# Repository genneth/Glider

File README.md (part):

# Glider

Open-source Eink monitor with an emphasis on low latency.

Note: This repo only contains the hardware design, the gateware running on the FPGA is my open-source [Caster EPDC](https://gitlab.com/zephray/Caster/) design. This README also contains information about the Caster as well.

This is a long document, containing not just information about this project, but also pretty much everything I know about Eink. Given it's a bit hard to gather information about Eink online, I think this is the right thing to do. Use the following table of contents to navigate around.

Eink is a registered trademark and brand of E Ink Corporation. All the contents provided in this repo are based on publicly available information online and original research. They are not endorsed by Eink in any way and they may contain errors and/ or inaccuracies. 

If you're interested in attaining a board, checkout the [product page for the Modos Paper Monitor on Crowd Supply](https://www.crowdsupply.com/modos-tech/modos-paper-monitor).

If you are interested in Eink or any other display technologies, I have a Discord server for that. Feel free to join: [https://discord.gg/rtT7euSHQS](https://discord.gg/rtT7euSHQS) . (This Discord server is also not endorsed by Eink or any other company. It's not a customer support server.) For Modos product support or other inqueries about Modos products, use [https://discord.gg/6ktE6VxSyh](https://discord.gg/6ktE6VxSyh).

## Table of Contents 

- [Overview](#overview)
    - [Features](#features)
    - [Hardware](#hardware)
    - [Components](#components)
- [Eink Screens](#eink-screens)
    - [Basic Theory of Operation](#basic-theory-of-operation)
    - [Advantages and Disadvantages](#advantages-and-disadvantages)
    - [The Role of Eink Controller](#the-role-of-eink-controller)
    - [Screen Panel Types](#screen-panel-types)
    - [Using Screen with Integrated Controller](#using-screen-with-integrated-controller)
    - [Using Screen without Integrated Controller](#using-screen-without-integrated-controller)
    - [Understanding Waveform](#understanding-waveform)
    - [Greyscale Display](#greyscale-display)
    - [Color Display](#color-display)
    - [Dithering](#dithering)
    - [Eink Screen Generations](#eink-screen-generations)
- [Caster/ Glider Design](#design-of-caster-and-glider)
    - [Low Latency Drive](#low-latency-drive)
    - [Hybrid Greyscale Mode](#hybrid-greyscale-mode)
    - [Limitations](#limitations)
    - [Hardware Design Decisions]()
    - [Gateware Architecture](#gateware-architecture)
    - [Firmware Functions](#firmware-functions)
    - [Resources Utilization](#resources-utilization)
- [Building](#building)
    - [PCB](#pcb)
    - [FPGA Bitstream](#fpga-bitstream)
    - [MCU Firmware](#mcu-firmware)
    - [Flashing Board](#flashing-board)
    - [Compatible Screens](#compatible-screens)
- [References](#references)
- [License](#license)
- [Appendix](#appendix)
    - [Using Screens without Datasheet](#using-screens-without-datasheet)
    - [Screen List](#screen-list)

## Overview

### Features

- Complete solution for low-latency/ high-refresh-rate EPD monitor
- Supports electrophoretic display panels with parallel I/F (Eink(R), OED and DES)
- Supports both monochrome and color-filter-array (such as Kaleido(TM)) based color screen
- Extremely low processing delay of \<20 us
- Supports binary, 4-level grayscale, and 16-level grayscale output modes
- Latency-optimized binary and 4-level grayscale driving modes
- Hybrid automatic binary and 16-level grayscale driving mode
- Host software runtime controllable regional update and mode switching
- Hardware bayer dithering, blue-noise dithering, and error-diffusion dithering with no additional latency
- Controller takes standard HVsync signal input
- Board-level design supports USB-C (USB Type-C DisplayPort Alt Mode) and DVI input

### Hardware

- Xilinx(R) Spartan-6 LX16 FPGA running Caster
- DDR3-800 framebuffer memory
- Type-C DisplayPort Alt-Mode video input with onboard PTN3460 DP-LVDS bridge or
- DVI (via microHDMI connector) video input with onboard ADV7611 decoder
- Epaper power supply with up to 1A peak current on +/-15V rail supporting large panels
- VCOM kick-back voltage measurement support
- On-board STM32H750 microcontroller for USB communication and firmware upgrade
- Up to 133MP/s processing rate with dithering enabled, >200MP/s when disabled

The board is designed with KiCad. You may need the latest stable version of KiCad to open the source file.

### Components

This repo hosts the PCB design and firmware source code. The RTL code is in a separate repo: [https://gitlab.com/zephray/Caster/](https://gitlab.com/zephray/Caster/).

## Eink Screens

Eink is the brand of a family of paper-like electrophoretic displays. The underlying technology is invented in the MIT Media Lab between 1995 and 1997 by Barrett Comiskey, J.D. Albert, and Joseph Jacobson. They later founded the E Ink Corporation to commercialize this technology.

Nowadays they are commonly used on e-readers and electronic shelf labels. You’ve probably seen them on Kindle, in stores, or maybe in some train stations as well.

| eReader/ Tablets | Electronic Shelf Label | Digital Signage |
|-|-|-|
|  |  |  |

(Source: https://www.eink.com/application, image copyright Eink corporation)

This section gives an overview of the electrophoretic displays, including the screen panels available and underlying technology. Note this project doesn't and can't support all electrophoretic screens. This documentation also solely focuses on using existing off-the-shelf screen panels rather than the physics or manufacturing process of one.

### Basic Theory of Operation

In the simplest form, you have charged particles with different colors, dispersed in some oil in some transparent container. By applying electric fields the particles can be moved up or down to produce either black or white, or a mixture of that.

(Source: https://www.eink.com/tech/detail/How_it_works , copyright Eink Corporation)

There are multiple technologies based on this basic concept, namely Eink’s micro-capsule display, SiPix (now acquired by Eink)’s micro-cup display, and WFT’s DES display. They differ in specific ways of confining the particles in containers, but otherwise very similar.

The pixels on the screen are typically arranged as a 2D array, driven with TFTs. The pixels are scanned/ driven periodically at a fixed refresh rate, typically ranging from 50Hz to 120Hz. Applying positive voltage on the pixel will typically drive the particles toward the white state while applying negative voltage will drive the particles towards the black state. This is similar to active matrix TN/IPS LCDs, which also use 2D TFT arrays and electrical fields for changing state. However, unlike LCDs, EPDs maintain their state after the electrical field is removed. So unlike LCDs which require continuous refreshing, the EPDs only need to be refreshed till the pixels are fully driven.

In terms of driving the screen panel, depending on the pixel value (1 or 0), each pixel would be driven either with a positive voltage or a negative voltage. A global counter can be used to count the frames elapsed and stop driving the pixels after a predefined period of time (for example, 100ms). Two framebuffers are typically used for determining if the pixel has changed color or not. If not, then the pixel does not need to be driven.

### Advantages and Disadvantages

In terms of display quality, EPDs are no match for modern IPS LCDs. The following is a comparison table of key parameters. The specific number would vary depending on the screen used but should be within the same ballpark.

| | Monochrome EPD | CFA-based Color EPD | Transmissive TFT IPS LCD | Reflective TFT TN LCD |
|-|-|-|-|-|
| Contrast Ratio | ~17:1 | ~14:1 | ~1000:1 | ~14:1 |
| Colors | 16 (Greyscale) | 4096 | 16M | 256 |
| Color Gamut | N/A | ~1.5% sRGB | ~99.9% sRGB | N/A |
| Reflectivity | ~45% | ~25% | N/A | ~15% |
| Response Time | ~150ms | ~150ms | ~10ms | ~15ms |

It has a few advantages. It reflects lights instead of emitting lights, so it generally consumes less power and can be used outdoors, etc. It’s also bistable, which means that it retains the image after the power has been removed. Personally, the biggest differentiating factor for me (author of this README) is that it looks like paper.

The image above shows a comparison between reflective TFT LCD (SHARP memory LCD in this case) and Eink. The LCD has a mirror-like texture which changes reflectivity drastically in different angles, while the Eink is more paper-like.

| ZBD LCD | Ch LCD | STN LCD |
|-|-|-|
|  |  |  |
| Bistable, reflective, high contrast, no greyscale, ~10s refresh | Bistable, reflective, lower contrast, up to 32 level greyscale, ~5s refresh | Volatile, reflective, lower contrast, up to 32 level greyscale, ~100ms response |

There are many other reflective or bistable display technologies. They are all interesting displays on their own, but none of them feels like paper (yet).

Overall, there is no single perfect display technology. Each has its own unique strength. Pick the right one for your project.

### The Role of Eink Controller

The Eink controller is in some ways similar to the display controller (DC/ CRTC) + timing controller (TCON) in a typical LCD-based system. It takes the raw image data and converts it to signals required to drive the screen.

To understand the actual work of an eink controller, start from the basic concept. The color of a pixel can be changed by applying positive or negative voltage for a finite period of time. From the controller’s perspective, depending on the current state of the pixel and the desired state of the pixel, there are 4 possibilities.

| Current State | Target State | Action |
|-|-|-|
| Black | Black | No operation |
| Black | White | Apply positive voltage |
| White | Black | Apply negative voltage |
| White | White | No operation |

The controller needs to store and maintain the screen state inside of its own buffer memory, so it would typically have a large on-chip SRAM or an off-chip SDRAM controller. The controller should also have a timer to ensure the screen doesn't get overdriven or underdriven.

The controller often uses the so-called "[waveform](#understanding-waveform)" to replace the action column of the previous table. Instead of hardcoding the action for state transition, the actions are stored into a look-up-table (LUT) which can be modified at runtime to allow higher flexibility.

Controllers may also offer more advanced features such as [dithering](#dithering) acceleration, multiple region updates, automatic LUT selection, etc.

### Screen Panel Types

As discussed in the previous section, an Eink screen needs to be coupled to an Eink controller to function. Aside from that, the screen also needs high-voltage drivers to drive the TFTs and the pixels. Virtually all E-paper panels use either COG (Chip-on-Glass) or TAB (Tape Auto Bonding) to integrate some chips onto the screen panel itself. Most of the screens available today can be divided into two categories based on whether or not the controller is integrated in:

Here is a non-exhaustive list of the types based on their size: (the size or resolution is not related to or limited by the type, it is just for a certain size, and the vendors tend to make them the same type.)

- Screens without controller: 4.3", 6.0", 7.8", 8.0", 9.7", 10.3", 13.3", 25.3", 31.2", 42"
- Screens with controller: 1.02", 1.54", 2.13", 2.6", 2.9", 3.71", 4.2", 5.65", 5.83", 7.5", 12.48"

One may notice that almost all e-readers/ e-ink cellphones use screens without controllers, while almost all e-ink electronic shelf labels (ESL) use screens with controllers. This gives some hints about the advantages and disadvantages of two types:

| | Without Controller | With Controller |
|-|-|-|
| System Cost | High. A dedicated controller or SoC with an integrated controller is usually required. Needs a dedicated power supply. | Low. Virtually any MCU could drive the screen directly, and the power supply is integrated in. |
| Greyscale Levels | Generally 16 (4bpp), up to 32 (5bpp) | Generally 2 (BW only) or 4 (2bpp), with some hack, up to 16 (4bpp) |
| Refresh Speed | Generally fast (100ms~300ms) for BW. Depends on the screen used and the system architecture | Generally fast (100ms~300ms) for BW if the partial refresh is enabled. Greyscales are much slower, BWR or BWY screens would be even slower.
| Total Update Latency | Generally the same as refresh time. Depends on the system architecture | Slow. Ranging from 100ms to several seconds based on the resolution. |

Please keep in mind the discussion is about off-the-shelf screens you can buy today. These tradeoffs do not necessarily come from the fact the controller is integrated or not.

Note that I mentioned the refresh speed and total update latency. They are different:

The refresh speed refers to the time it takes to start refreshing the screen: from starting to seeing screen changing, to the screen finish showing the new content.

The total update latency refers to the latency when the processor needs to update the screen, to the screen finish showing the new content. As you can see, this is the biggest issue for screens with controllers. This is the main reason why they are rarely used on e-readers cell phones or PC monitors.

This diagram illustrates the difference between the two. It should be noted that the screens without controllers have the flexibility to be driven quickly, but the system designer might not architect the system for low latency.

### Using Screen with Integrated Controller

Screens with integrated controllers have almost everything already integrated. Common display panels of this type only need a few external capacitors, inductors, and MOSFETs to support the integrated bipolar power supply circuit, then it could be hooked up to MCUs or MPUs using common interfaces like SPI or I2C. There are a lot of driving boards and examples of these screens available online.

To be expanded (TODO)

### Using Screen without Integrated Controller

This could get complicated. Note I used a lot of "generally" in the previous comparison table because there are many things one could do to drive them. Some of them would certainly impact the performance. The main issue here is the controller chip. There are three solutions to drive these screens:

- Using a dedicated controller chip to drive the screen
- Using an SoC that has an integrated controller
- Using a fast MCU/SoC to emulate the controller with GPIO (software timing controller)

Then, again here is a comparison between them:

| | Specialized controller chip | SoC with integrated controller | MCU + Software TCON |
|-|-|-|-|
| Resolution | UXGA+ | UXGA+ | Limited by MCU RAM. Up to XGA with SRAM, UXGA with PSRAM, UXGA+ with DDR |
| Greyscale | Up to 32 | Up to 32 | Up to 32 |
| Partial Update | Yes | Yes | Yes |
| Total Update Latency | Depends. Could be very close to refresh speed, could be slow like screens with controller | Same as refresh speed | Same as refresh speed if data is internally generated (not streaming from an external device such as a PC) |
| Suitable Applications | IoT devices, E-readers, cellphones, E-ink monitors. possibly E-ink laptops | Advanced IoT devices, E-readers, cellphones, E-ink typewriters, possibly lower performance E-ink laptops | When using MCU: IoT devices, large ESLs, simple DIY E-readers. When using MPU: Same as SoC with integrated controller |

When using a dedicated controller, it could accept data from external devices. This allows it to be used in various different types of applications. Ranging from IoT devices, and ESLs, to PC monitors with relatively fast refresh rate and low latency.

When using SoC or MCU, the display content is generated by the SoC or MCU itself, which ultimately is limited by the capability of the SoC or MCU. Given the current SoCs with E-ink display controllers are usually limited in performance, the application is limited. The same goes for MCU, it does what an MCU could do. You could find ways to stream video data into SoC or MCUs by using USB, camera interface, WiFi, etc., but this might not be optimal.

#### Existing Solutions

- Specialized controller chip
    - Closed-source
        - EPSON S1D13xxx: Widely used EPD controller in early E-readers. Proprietary, no documents available. Probably EOL.
        - IT8951: Used on the waveshare EPD Hat. Documents are available. It works with large EPDs up to 2048x2048. The drawback is the speed as the interface between processor and IT8951 could be slow. This is similar to the situation on screens with integrated controller
        - T1000: Also known as IT8957, upgraded model of IT8951. It supports even higher resolution. It features a higher speed MIPI DSI interface to mitigate the slow speed of IT8951.
        - Waveshare HDMI driver board: FPGA-based controller. Closed source but easily purchasable, could be integrated into larger projects as a module.
    - Open-source
        - This project (Caster + Glider): FPGA-based controller, multiple update modes, ultra-low latency processing, and wide range of screen support.
        - https://hackaday.io/project/21607-paperback-a-desktop-epaper-monitor: FPGA-based controller. However, doesn't support partial update mode and slower speed.
        - https://hackaday.io/project/21168-fpga-eink-controller: FPGA-based controller supports vendor waveform with reasonable speed.
- SoC with integrated controller
    - RK29xx: Fairly old, Cortex-A8 based (RPi 1 level performance), 55nm, EOL
    - RK3026/RK3028: Fairly old, Cortex-A9 based (RPi 2 level performance), 40nm, EOL
    - i.MX 50: Fairly old, Cortex-A8 based (RPi 1 level performance), 65nm, in production
    - i.MX 6ULL: Cortex-A7 based (RPi 1 level performance), 40nm, in production
    - i.MX 6S/D: Fairly old, Cortex-A9 based (RPi 2-3 level performance), 40nm, in production
    - i.MX 7S/D: Cortex-A7 based (RPi 2 level performance), 28nm, in production
    - i.MX 8ULP: Cortex-A35 based (RPi 2 level performance), 28nm FD-SOI, in production
    - AW B200: Cortex-A53 based (RPi 2 level performance), 28nm, in production
    - MT8113: Cortex-A53 based (RPi 2 level performance), 12nm, in production
    - RK3566/RK3568: Cortex-A55 based (RPi 3 level performance), 22nm, in production
    - RK3576: Cortex-A72 + A53 based (RPi 4-5 level performance), 8nm, in production
- MCU/SoC + Software TCON
    - http://essentialscrap.com/eink/waveforms.html: One of the earliest e-ink hacks. Limited in performance but still could be used as a reference
    - NekoCal: One of the earliest e-ink software TCON with greyscale support. Used to be available as a DIY kit. No longer updated, still could be used as a reference
    - InkPlate 6/10: Commercially available. Based on ESP32.
    - EPDiy: Based on ESP32, supports a lot of different screens, recommended if want to build some device with ESP32+Eink or embed it into a larger project.

#### Interface Signals and Timing

The interface signals and timing are fairly similar to LCDs without a controller. Following is the list of signals typically found on EPDs:

- GDOE/ MODE: Gate driver output enable
- GDCLK/ CKV: Gate driver clock (like HSYNC in LCD)
- GDSP/ SPV: Gate driver start pulse (like VSYNC in LCD)
- SDCLK/ XCL: Source driver clock (like PCLK in LCD)
- SDLE/ XLE: Source driver latch enable (like HSYNC in LCD)
- SDOE/ XOE: Source driver output enable
- SDCE/ XSTL: Source driver start pulse (like DE in LCD)
- SD: Source driver data (8-bit or 16-bit)

SD signals go into the source driver, typically in the X direction. GD signals go into the gate driver, typically in the Y direction. It's a 2D array, the gate driver selects one line at a time, and the source driver outputs the voltage for all the pixels in that line.

Conceptually, it's like a raster scan on a CRT. To send one field of data, both GD and SD are reset to the start position by using the start pulse signal. Data are then transmitted into the source driver 4 or 8 pixels at a time. Once the line has been fully transmitted, the source driver is reset to the beginning position by a start pulse signal, and the gate driver moves to the next line by a pulse on the gate driver clock. Once all lines have been scanned, the entire process repeats for the next field.

One notable difference with LCD is that each pixel is represented by 2 bits. This, however, doesn't mean each pixel is 2bpp or 4-level greyscale. The 2-bit per pixel is used to encode the voltage applied to the pixel:

- 00: No voltage
- 01: Negative voltage
- 10: Positive voltage
- 11: No voltage

Just like CRT/ LCD, there are also blanking periods in the entire timing (which means it's just waiting without active pixel data being sent). They have identical meanings to CRT/ LCD systems:

(Source: https://projectf.io/posts/video-timings-vga-720p-1080p/, Copyright Will Green)

The following is a piece of pseudo-code implementing the Eink timing:

```c
#define DATA_BUS_WIDTH      8 // 8bit wide bus
#define PIXEL_PER_CYCLE     (DATA_BUS_WIDTH / 2)
#define VFP     12  // Vertical front porch
#define VSYNC   1   // Vertical sync length
#define VBP     2   // Vertical back porch
#define VACT    758 // Vertical active lines
#define HFP     72  // Horizontal front porch
#define HSYNC   2   // Horizontal sync length
#define HBP     2   // Horizontal back porch
#define HACT    (1024 / PIXEL_PER_CYCLE)

void pulse_h_clock() {
    sdclk = 1;
    sdclk = 0;
}

void drive_line(bool v_in_act) {
    sdce = 1;
    gdclk = 0;
    for (int i = 0; i < HFP; i++) pulse_h_clock();
    sdle = 1;
    gdclk = 1;
    for (int i = 0; i < HSYNC; i++) pulse_h_clock();
    sdle = 0;
    for (int i = 0; i < HBP; i++) pulse_h_clock();
    if (v_in_act) sdce = 0;
    for (int i = 0; i < HACT; i++) {
        send_data();
        pulse_h_clock();
    }
}

void drive_frame() {
    gdoe = 0;
    sdoe = 0;
    gdsp = 1;
    for (int i = 0; i < VFP; i++) drive_line(false);
    gdsp = 0;
    gdoe = 1;
    sdoe = 1;
    for (int i = 0; i < VSYNC; i++) drive_line(false);
    gdsp = 1;
    for (int i = 0; i < VBP; i++) drive_line(false);
    for (int i = 0; i < VACT; i++) drive_line(true);
}
```

More explanation can be found at [http://essentialscrap.com/eink/index.html](http://essentialscrap.com/eink/index.html)

### Understanding Waveform

The waveform is a look-up table for the eink controller to determine how to drive the pixels, mostly useful for greyscale image display, but generally used for binary image display as well.

The look-up-table has 3 inputs (dimensions): frame number, source grayscale level, and destination grayscale level. During the update process, for a certain pixel, the source and destination level stays the same, and the frame number increases each frame. The look-up process is done for every pixel every frame. The controller may choose different LUTs depending on the ambient temperature. Mode switching is also implemented by simply switching between different LUTs.

This is essentially what typically eink controller does. For each pixel, look up in the table to determine the voltage to use. Repeat this for a couple of frames with an incrementing frame counter, until all pixels are fully driven.

It should be obvious that the waveform file itself is independent of the resolution as the waveform only cares about a single pixel. With an incorrect or un-optimal waveform, the screen should at least display some recognizable image.

#### Waveform Example

There are several sample waveform tables provided in the project repo. Take the GC16 (Greyscale clearing 16-level) waveform of GDEW101C01 as an example: https://github.com/zephray/NekoInk/blob/master/waveform/gdew101_gd/test_M2_T0.csv

Take one line from that file:

```6,13,0,0,0,0,0,0,0,0,0,2,1,1,1,1,1,1,1,1,1,1,2,2,2,2,2,2,2,2,2,2,2,2,2,2,2,2,1,0```

This means from greyscale level 6 to level 13, it needs to go through the following sequence. Each number means the operation on that frame, 0 is no-operation, 1 is darken, and 2 is lighten. In this case, there are 38 frames, first 9 frames do nothing, then lighten for 1 frame, darken for 10 frames, lighten for 16 frames, and finally darken for 1 frame and have no operation for the last frame. This is the sequence to change a pixel from level 6 to level 13. Such lookup is done for every pixel on every frame.

#### Waveform Modes

To give system designers more flexibility, Eink controllers often offer multiple "modes", like binary mode, 16-level grayscale mode, 16-level grayscale mode with reduced flashing, 4-level grayscale mode, etc.

The waveform provided by Eink has many modes. There is a good document from Eink describing the modes:

https://www.waveshare.net/w/upload/c/c4/E-paper-mode-declaration.pdf

It provides a good overview of the modes. I am just going to add some comments.

- GC in the GC16 stands for "greyscale clearing". GC does not stand for greyscale. There are 16-level greyscale modes that aren't called GC16.
- Officially there are no 32-level greyscale modes (yet). There are 5-bit waveforms, which means they internally use 5 bits for each pixel, which potentially allows up to 32-level greyscale, but no such waveform exists (yet).
- There are no 16-level greyscale modes without flashing. The DU4 is the only greyscale mode that's non-flashing.
- The GL16 mode, as described, only works for black text on a white background. When refreshing greyscale images, the GL16 is similar to the GC16.
- The GLR16 mode is also called the REGAL mode, and the GLD16 mode is also called the REGAL-D mode.
- Eink doesn't even know if it should be spelled as REAGL or REGAL:  Google search "REAGL site:eink.com" and "REGAL site:eink.com" both returned several results.
- Eink-provided waveform usually implements all these modes, however it is not always required. The waveform file may also contain waveform tables in other orders.
- In terms of the waveform, the waveform for GL16, GLR16, and GLD16 are identical. This is expected, the REGAL requires an additional algorithm on the host image processing and is not a technology based on tweaking the waveform.

#### Obtaining Waveform

In general, the screen vendor (Eink, Good Display, etc.) should provide the waveform file.

If your screen has a flash chip on it, it's also possible to extract the waveform from a flash dump:

```dd if=somedump.bin of=waveform.wbf bs=1 skip=2182```

If you have access to an application board, it might also be possible to extract the waveform there. For example, if the system uses a T1000/T2000/T2001 controller, the waveform is usually stored in the SPI flash connected to the controller. Some times the waveform stored on the flash is compressed (in addition to the RLE compression already applied to the waveform file itself).

#### Waveform Formats

E-Ink distributes waveforms in the wbf file format. SoC/ Eink controller hardware often requires converting the file into a vendor-specific file format. Caster/ Glider also uses a specific binary format. This project defines a common human-readable format (Interchangeable Waveform Format, IWF) and provides several tools for working with different binary formats and the IWF format.

#### Interchangeable Waveform Format

The waveform consists of one descriptor file in iwf extension (ini format) and various lut data files in csv format.

The descriptor contains the following required fields:

- VERSION: the version of the descriptor (should be 2.0)
- NAME: (optional) original name for the waveform
- BPP: (optional, default 4) 4 or 5, representing the internal state count used for waveform
- PREFIX: the filename prefix for actual waveform files
- MODES: the total modes supported by the waveform
- TEMPS: the total number of temperature ranges supported by the waveform
- TxRANGE: the supported temperature in degC, where x is the temperature ID
- TUPBOUND: (optional) upper bound for temperature range, each range is TxRANGE to Tx+1RANGE (or TUPBOUND in case of the last one)
- TABLES: total number of LUTs inside the waveform
- TBxFC: the frame count for the table, where x is the LUT ID

Each mode has its own mode section named [MODEx], where x is the mode ID, containing the following fields:

- NAME: the name for that mode
- T*TABLE: the table used for the temperature in that mode

There should be a number of LUTs, saved in the filename like PREFIX_TBx.csv, where x is the LUT ID. Each csv file should contain a LUT like this: lut[src][dst][frame], which means, to transition from src greyscale level to dst greyscale level, at a certain frame in a frame sequence, what voltage should be applied to the screen (0/3: GND / Keep, 1: VNEG / To black, 2: VPOS / To white). Each line contains the frame sequence for one or more source-to-destination pairs.

For example:

- ```4,7,1,1,1,0,2``` means to transition from greyscale level 4 to greyscale level 7, there should be 5 frames, each applying VNEG VNEG VNEG GND VPOS
- ```0:14,15,2,2,2``` means to transition from any greyscale level between 0 and 14 to greyscale level 15, there should be 3 frames, each applying VPOS VPOS VPOS

These are provided to only illustrate the file format, they are not valid or meaningful Eink driving sequences.

#### Converting Between Waveform Formats

The following converters are provided in the repo:

- To convert from iwf to fw (iMX6/7 EPDC format): ```./mxc_wvfm_asm v1/v2 input.iwf output.fw```
- To convert from fw to iwf: ```./mxc_wvfm_dump v1/v2 input.fw output_prefix```
- To convert from wbf to iwf: ```./wbf_wvfm_dump input.wbf output_prefix```

#### Waveform Tweaks

Some commercial implementations allow users to reduce the frame count and/ or alter the waveform playback speed, so the user can trade between contrast ratio and frame rate.

### Greyscale Display

Other than full white and full black, with appropriate modulation, Eink screens can also display some levels of greyscale (typically 16).

For grayscale displays, the basic idea is simple. If the pixel is not fully driven (say only drives for 50ms while it takes 100ms to reach full black/ white), it would stay in a gray state.

There are two ways of achieving this modulation:
- Modulate the frame time
- Modulate the number of frames with constant frame rate

Both are possible, as described below

#### Frame Time Modulation

This method changes the drive time by changing the length of a single frame. The screen would only be driven for 15 or 31 frames for 16-level and 32-level greyscale, but the frame time (thus frame rate) is altered to provide the desired driving time. The LUT would be a one-dimension look-up table, only containing the incremental time required to drive to the next greyscale level. The source/ gate driver output enables the line to be toggled to achieve the desired driving time.

This method doesn't seem to be implemented in any commercial solutions and is significantly slower than the second method. But it certainly works. The 32-level greyscale demo shown in the picture above is achieved using this method.

#### Frame Count Modulation

This method changes the drive time by changing the number of frames being applied to the screen. The screen is still being driven at a constant frame rate. The following is a simplified hypothetical waveform table for achieving 4-level greyscale:

| Previous State | Target State | Frame 0 | Frame 1 | Frame 2 | Frame 3 | Frame 4|
|-|-|-|-|-|-|-|
| Black | Black | NOP | NOP| NOP | NOP | NOP |
| Black | Dark Grey | VPOS | VNEG | VPOS | NOP | NOP |
| Black | Light Grey | VPOS | VNEG | VPOS | VPOS | NOP |
| Black | White | VPOS | VNEG | VPOS | VPOS | VPOS |

Note how it alternates between VPOS and VNEG in the beginning. This is often called the "activation phase" to improve the contrast ratio. Putting this detail aside, it changes the number of VPOS frames to settle down on different grey levels.

The actual grayscale driving sequence used in the commercial implementation is more complex than that, often involving switching the pixel towards black/white a few times before settling. This design is partially due to the limited time control granularity and other temperature/ manufacturing variance-related concerns. Some side-effects of such a driving sequence are that the refreshing process is “flashing”, and is slower compared to displaying only a 1-bit binary image.

### Color Display

There are several different technologies that could be used to build full-color EPDs. The 2 most common ways are to use a color-filter-array (CFA) or use a multi-pigment color display.

The following picture has a CFA-based color screen (Kaleido 3) on the left, and a multiple pigment color display (Spectra 6) on the right, displaying the same image.

(Yes the left one IS a color screen!)

#### Color Filter Array

CFA stands for color filter array, which is colored glass/ film on top of the screen pixel. This is also the technology used on most color LCDs. Eink Kaleido, Eink Triton, and color DES are based on this technology. The main advantage is that it's relatively simple to control, and the low-level driving is the same with the greyscale panels. Thus it has the same level of refreshing time (100~200ms), and the same level of greyscale (16 level translate to 16^3=4096 colors). The drawback is that the CFA filters out some light (due to its colored nature), and the screen reflectivity is negatively affected by the CFA. The screen ends up being quite dark. Up to now, most color E-readers use CFA-based displays. This project supports all three major types of CFA-based EPD screens: color DES screen, Eink Triton, and Eink Kaleido.

#### Case Study: GDEW101C01 (CFA-based, DES)

The GDEW101C01 is a 10.1" color DES screen made by Good Display / WeiFeng Tech. It uses CFA to produce color images. As a result, to the eink controller hardware, it's just a normal greyscale panel with a bunch of pixels. However, the pixels are colored depending on their location due to the CFA. The coloring of the pixels can be either handled by hardware or software.

##### Pixel Arrangement

Color DES is a bit different from a typical color TFT LCD in terms of CFA design. Typically on TFT LCDs, one RGB pixel is called a pixel, and each R/G/B component is called as a sub-pixel. On color DES, the sub-pixel ends up being called a pixel, and each pixel is either red, green, or blue. In the display industry, such pixels are more commonly referred to as dots.

Pengo, CC BY-SA 3.0 https://creativecommons.org/licenses/by-sa/3.0, via Wikimedia Commons

The actual photo of the DES panel under the microscope:

In the above photo, the DES pixel arrangement is the same as the OLPC XO-1. Notably, many Eink's Kaleido 3 (but not all) also uses the same pixel arrangement.

Having no subpixel / each pixel only has 1 color doesn't necessarily mean that the effective resolution needs to be divided by 3. This arrangement is slightly more "efficient" than the RGB strip in terms of perceptive resolution. You can find a more detailed analysis in the paper Comparing the Effective Resolution of Various RGB Subpixel Layout.

##### Processing image for Color DES

If the image is displayed on color DES without any processing, it would look like a greyscale image. This is similar to when you just send the same color value to R/G/B components on a color LCD.

To get color, there are 2 possible solutions:
- Treat 4 pixels as a group of a single pixel, and each physical pixel is now considered as a subpixel.
- Treat each pixel as an independent pixel, but send only the color component that corresponds to the pixel color.

Depending on how you classify pixel and subpixel, the 2nd method can also be viewed as a mean of 2X supersampling subpixel rendering.

In general the 2nd method offers better resolution especially in text:

| Method 1 | Method 2 |
|-|-|
|  |  |

The following discussion are all about the 2nd method: render at full resolution, but only use 1 color component for each pixel.

(Source: https://wiki.laptop.org/go/File:PixelLayoutDiagonal.png, public domain)

For example, for pixel 01, the pixel on the screen is green. Then only the green component from the frame buffer should be sent to the screen.

To get a basic 4096 color image display, this is everything needed. However generally to improve image quality, a few more steps are applied:

##### Low pass filtering

The previously described image-displaying process is essentially a down-sampling process for each color component: Only 1/3 of the pixels are sent to the screen. Then this becomes a classic signal processing issue: sampling the signal would cause frequency components above Nyquist to fold back to the low frequency part. Or in simpler words, you would see jagged edges/ aliasing, which are things that weren't present in the original image. To prevent this, low pass filtering (blurring) needs to be applied first to the image to remove these high-frequency components. The following diagram from the OLPC wiki shows a simple way of implementing a such filter:

(Source: https://wiki.laptop.org/go/File:PixelProcDiagonal.png, public domain)

##### Dithering

Dithering can be applied to further improve image quality. See the dithering section for more details.

#### Multi-Pigment Color Display

Another technology for implementing color EPD is by using a multi-pigment color display. This is a technology developed initially by SiPix and further improved by Eink. The basic idea is to use ink particles with different colors inside a single pixel. By applying a sequence of voltages, the ink particles can be arranged to display different colors.

(Source: https://www.eink.com/tech/detail/How_it_works , copyright Eink Corporation)

One major advantage of this solution is it can achieve higher resolution (because it doesn't have a CFA, so no resolution reduction), higher reflectivity (because it doesn't have a CFA, so no light loss), and higher color saturation (because it doesn't have a CFA, no need to play the reflectivity vs saturation trade-off game).

Eink has 2 lines of products using this Technology, Eink Gallery and Eink Spectra. The advantage is it's much brighter compared to CFA-based solutions. The disadvantage is it's much more difficult to drive, and quite slow: 1st /2nd gen Eink Gallery screen takes 30s (!) to refresh, and Spectra 6 Plus devices take 7s to refresh. It's possible to trade in some color saturation for higher speed, though still much slower than CFA-based solutions. The specific product lines will also be discussed in [Eink Screen Generations](#eink-screen-generations)

##### How ACeP Waveform Works

To be written (TODO)

##### How to get more colors on ACeP

This is possible with a modified waveform.

To be written (TODO)

##### Fast ACeP

While ACeP screens have been generally slow to refresh (15-30s), Eink has tried to improve that. In 2022 Eink released their Gallery 3 lines of ACeP screens, which promised sub 1 second update time. [ACeP was supposed to be the "next big thing" in ereader](https://arstechnica.com/gadgets/2022/04/new-e-ink-gallery-displays-could-finally-make-full-color-e-readers-good/). Back in the end 2022, Eink announced that ["Gallery 3 has moved into mass production, with customer products from Bigme, BOOX, iFlyTek, iReader, PocketBook, Readmoo, and AOC coming down the pipeline in 2023 and beyond"](https://www.e-ink-info.com/e-ink-gallery-3-acep-color-epaper-displays-move-mass-production).

How well does it do? Just talking about the screen, it's not looking good. It suffers from poor reflectivity and poor saturation to a point where it's not much better than Kaleido:

(Original illustration copyright MiHoYo)

The difference between Gallery 3 and Gallery Palette (which is supposed to be a lower-end product) is also stunning:

The one on the left is the Gallery 3 used on eReaders, and the one on the right (brighter and more saturated one) is the Gallery Palette used on ESLs. Though to be honest I hacked the right one a bit to display 512 colors opposed to the stock 7 colors. If Gallery 3 had the same image quality as previous ACeP/ Gallery screens, it would make sense to trade in response time for better image quality. But it doesn't.

##### Future of ACeP

While as previously referenced that Eink was hoping to ship lot of Gallery 3 based E-readers in 2023, 2023 passed with exactly one product, the Bigme Galy, with mixed receptions. Early 2024, it was announced that [Bigme Galy has been discontinued](https://goodereader.com/blog/electronic-readers/bigme-galy-is-discontinued), and [Eink has announced EOL for certain ACeP-based products](https://www.ineltek.com/wp-content/uploads/2024/04/EInk_AC073TC1_EOLNoticeLetter_notice_20240401.pdf). But ACeP is not dead yet.

Going forward, Eink has 3 different line-ups for different markets:
- Eink Marquee for outdoor signage
- Eink Spectra for electronic shelf labels and advertisements
- Eink Gallery for e-readers and e-notebooks

All of these lines are direct offspring of the original ACeP screens:
- Eink Marquee uses the same color composition as the ACeP, but replaces the SiPix-style micro-cup with micro-capsule
- Eink Spectra uses similar structure as the ACeP, but replaces color composition
- Eink Gallery is the original ACeP line up

In 2024, we saw the release of reMarkable Paper Pro, which is a 11.8" Gallery 3 e-notebook. ACeP screens are still in production and we might be able to see more products in the future.

##### Spectra 6

Compared to the Gallery lines, Spectra 6 uses a very similar multiple pigment system. But instead of using cyan, magenta, and yellow as the base colors, Eink switched to use red, yellow, and blue instead. Officially the color gamut volume stays the same, but the contrast ratio gets boosted up to 22:1 from 10:1, mainly due to darker black. Reflectivity stays the same at around 35%, lower than Carta products, but still far better than CFA based ones.

(TODO: Compare image quality between Sp6 and GalleryPlus)

### Dithering

Eink and DES panels typically only support up to 16 levels of greyscale with the vendor-provided waveform. To improve response time, or to avoid flashing images, a binary (1-bit, 2-level) display is also used. Dithering could be applied to produce better images (increasing SNR, in signal processing sense).

The following is applying dithering to a simple black-to-white gradient. Note the results are not optimal due to limitations in quantization and incorrect gamma correction. But the idea is the same.

| Original | Binary No-dithering | 2 Row Sierra Dithered |
|-|-|-|
|  |  |  |

Dithering can help when the screen has a native 16-level greyscale as well:

| Original | 16 Level Greyscale No-dithering | 16 Level Greyscale Dithered |
|-|-|-|
|  |  |  |

As you can see, the non-dithered image loses all the greyscale in between, while the dithered version on the right gives the illusion of greyscale while only using full black and full white colors.

To understand it further, take the following example:

Say the source image is 30% brightness (or 0.3). This cannot be displayed on a binary screen which can only display 0% (0.0, black) or 100% (1.0, white) brightness. A simple thresholding process is added to determine if the screen should display 0 or 1 by checking the incoming brightness. If it's less than 0.5 then the display brightness is rounded down to 0, otherwise 1. Because 0.3 is always lower than 0.5, the whole screen displays 0 (black).

This is less than ideal. A better way is to set around 30% of the pixel black, while 70% of the pixel white. Different dithering algorithms can be used to achieve this 30/70 distribution. Two common methods used are ordered dithering and error-diffusion dithering, which will be described below.

#### Ordered Dithering

The ordered dithering adds a pre-computed/ fixed texture to the image before the thresholding process. In other words, it basically adds some noise to the image. This may sound weird initially, but it should be easy to see the effect of noise in the example.

Using the example previously described displaying 30% brightness grey on a binary screen. The goal is to let the rounding process end up with 0 for 30% of the time and 1 for 70% of the time. This could be achieved by adding a noise. In the simplest case, a random number with a uniform distribution between [-0.5, 0.5] is added to the incoming brightness. The brightness has a value of 0.3, when adding this number to the random number, the random number now has a uniform distribution between [-0.2, 0.8]. The threshold is still set to 0.5, and now the probability distribution can be seen as below:

The pixel now has a 30% chance of being rounded up to 1, and a 70% chance of being rounded down to 0. Before dithering, it would always be rounded down to 0.

However, a purely random number is generally not the best noise to use. Bayer dithering matrix and blue noise are more commonly used, with the results as illustrated below. The idea is the same, but instead of adding random numbers, a pre-computed number from the Bayer dithering matrix (array) or blue noise texture (array) is added to the image.

| Random Dithering| Bayer Dithering | Blue-noise Dithering |
|-|-|-|
|  |  |  |

#### Error-Diffusion Dithering

The basic idea is when rounding down the color (selecting the closest color from the 16-level greyscale from 256-level input), the error value (difference) is calculated and added to neighboring pixels (so this error would be considered when processing these pixels later). The whole process is called error-diffusion.

Still using the previous example of a 30% brightness image, and assume an extremely simple dither kernel: diffuse all error to the next pixel. Let's see it in action.

In the first pixel, 0.3 (image brightness) is less than 0.5 (threshold), so it's displayed as 0 (black). This introduces a 0.3 error: the displayed color is 0.3 darker than the requested color. So 0.3 is being diffused to the next pixel, hoping the next pixel can correct the error.

Onto the second pixel. The value is 0.3 (image brightness) + 0.3 (diffused error) = 0.6. It's now larger than 0.5 (threshold), so it's displayed as 1 (white). This introduces a -0.4 error: the displayed color is 0.4 brighter than the requested color. -0.4 will be diffused to the next pixel.

For the 3rd pixel, the value is now 0.3 - 0.4 = -0.1. This is less than 0.5 and displayed as 0 (black). Error -0.1 is diffused further.

And this process just goes on. With enough pixels, eventually, it would yield about 30% of white pixels and 70% of dark pixels.

Similar to how random value is not the best thing to do in ordered dithering, dithering to the right is also less than ideal. It creates very repetitive patterns. I mentioned the word kernel. Error diffusing uses a diffusion kernel, which specifies the target and percentage of the diffused error. There are many classic kernels, such as Floyd-Steinberg, Stucki, Sierra, etc. commonly used for image dithering. They all diffuse to more than 1 pixel to improve the overall look of the image. As shown below, even just diffusing the error to 2 pixels (half of the error goes to the pixel on the right, and the rest half of the error goes to the pixel on the bottom) yields a much better result:

| Dither to Right | Right and Down | Floyd-Steinberg |
|-|-|-|
|  |  |  |

#### Applying Dithering on CFA-based Color Screens

Dithering can be applied on CFA-based color screens such as Eink Kaleido and color DES screens as well. The following is on a simulated DES screen: (The left original is assuming the screen has a native 24bpp color, still on a simulated screen)

| 16M color DES (does not exist) | 8-color DES | 8-color DES Dithered |
|-|-|-|
|  |  |  |

Ordinary dithering kernels don't work too well on color screens. For example, the error-diffusion dithering process pushes/ diffuses error neighboring pixels without considering their color. Ideally, it should push/ diffuse the error only to pixels with the same color. This is fairly easy to fix though, by tweaking the kernel it would achieve good results on CFA-based screens as well. (I am going to shamelessly call it Wenting's kernel)

| 16M color DES (does not exist) | 8-color DES naively apply Floyd-Steinberg (wrong) | 8-color DES with Wenting's kernel |
|-|-|-|
|  |  |  |

Of course, one can apply Bayer-like ordered dithering, blue noise dithering, or dithering on 4096-color mode as well:

| 8-color DES Bayer-like | 8-color DES Blue-noise | 4096-color DES Error-diffusion |
|-|-|-|
|  |  |  |

It's called bayer because, similar to how naively doing error diffusion doesn't work, the bayer matrix has to be modified to work on the color screen.

#### Gamma Correction

Another thing to consider is gamma. The dithering process involves a step of selecting the closest value. However, selecting the closest numerical value does not necessarily mean the closest color. The image typically is in sRGB space, which is non-linear. This causes the simple rounding to pick the wrong color, also calculating the wrong error value. One solution is to work in the linear space. This is also known as gamma-aware dithering. You could read more related info online, for example here: [https://learnopengl.com/Advanced-Lighting/Gamma-Correction](https://learnopengl.com/Advanced-Lighting/Gamma-Correction).

The difference is quite evident when dithering down to 1 bit for a color screen. The top left is the original image, the top right is dithering in the sRGB space, and the bottom left is dithering in the linear space.

#### Further Reading

See [https://en.wikipedia.org/wiki/Dither](https://en.wikipedia.org/wiki/Dither) for more information about dithering.

### Eink Screen Generations

Depending on how you count, there are multiple generations of Eink screens commercially available. For monochrome screens before 2023, it's possible to tell the generation by looking at the 6th digit on the serial number:

That is the FPL code in the following table:

| FPL Platform | FPL Code | Panel Model    | Marketing Name          | First Introduced |
| ------------ | -------- | -------------- | ----------------------- | ---------------- |
| 2.0          | 0        |                |                         | ?                |
| 2.1          | 1        |                |                         | 2004             |
| 2.3          | 2        |                |                         | ?                |
| V100         | 3        |                | Vizplex                 | 2007             |
| V110         | 4        |                | Vizplex                 | 2008             |
| V110A        | 5        |                | Vizplex                 | 2008             |
| V220         | 6        | VA3200         | Pearl                   | 2010             |
| V250         | 7        |                | Pearl                   | ?                |
| V220E        | 8        |                | Pearl                   | ?                |
| V320         | 9, R     | VB3300         | Carta 1.2 / 1000        | 2013             |
| V320         | ?        | VB3300?        | Carta 1100              | 2019             |
| V400         | A, C     | VD1400/ VD1405 | Roadrunner / Carta 1200 | 2021             |
| V450         | ?        | VH1948         | Carta 1250              | 2021?            |
| ?            | ?        | VD1400/ VD1405 | Carta 1300              | 2023             |
| ?            | M        | ?              | Spectra (BWR)           | ?                |

Data points used to create the table above:
- The first commercialized Eink e-reader SONY Librie hit the market in 2004, *likely* with an ED060SC1 panel
- ED060SC1 has an FPL code of 1 on the barcode, meaning the 2.1 platform
- Multiple datasheets (like the one for ED060SC4) confirms the 6th digit marks the FPL code with mapping for V220/220E/320/400
- Inkwave's WBF decoder (originated from Kindle GPL kernel code) provides an FPL platform to an FPL code mapping table that matches well with info from the datasheet
- Kindle Oasis3 was reported to use a Carta 1100 screen, and it has an ED070KC3 screen with a V320 FPL platform
- Kindle PW5 was reported to use a Carta 1200 screen, and it has an ED068KC5 with a VD1405 panel model
- Kobo Clara BW was reported to use a Carta 1300 screen, and it has an ED060KHE with a VD1405 panel model
- The datasheet of ED068KC1 mentioned the name "Roadrunner" for the 400 platform, but that name never gets used outside of that. I would guess they were going to use the Roadrunner for the new generation but eventually fell back to Carta 1200 so it's more like an incremental improvement
- From the information available, it really looks like Carta 1000 and 1100 use the same film, and Carta 1200 and 1300 use the same film. If this is true, it may sound like a scam if they are named differently but use the same film. But this is actually okay. Just like how chips usually have a binning process, the same chip would sell under different product names with different performance levels. It's reasonable for Eink to do incremental improvements on the manufacturing process to yield better screens with the same film and call it under a different name, or simply binning screens to different grades and selling under different names.

I will let you decide how to count the generations.

For the CFA-based screens, the following generations of screens exist:

- Eink Triton: First generation color screen. Uses an RGBW glass color filter and square pixels. The underlying screen panel uses Pearl film.
- Eink Triton 2: 2nd generation color screen. Uses RGB glass color filter and stripe pixel. The underlying screen panel uses Pearl film.
- Eink Kaleido: 3rd or 2nd gen color screen depending on the definition. Uses an RGB color filter. Each pixel is still square, but each color covers 3 pixels. The underlying screen panel uses Carta film.
- Eink Kaleido Plus: 2nd gen Kaleido. Uses an RGB color filter. Each pixel is still square but different configurations exist. Some screens have each color covering 2 pixels, some others have each color covering only 1 pixel. The underlying screen panel uses Carta film.
- Eink Kaleido 3: 3rd gen Kaleido. There are at least 2 different configurations exist. One features RGB filter covering 1 pixel per color, the other features a 2R/2G/1B configuration, on average 5/3 pixels per color. The underlying screen panel uses Carta 1000/1200/1250/1300 film depending on the model.
- Eink Kaleido 3 Outdoor: Wide temperature version of Kaleido 3.

Most CFA-based color screen panels don't come with an integrated controller, but there are a few exceptions.

For the multiple-pigment color screens based on SiPix technology, the following generations of screens exist:

(Color abbreviation: B: black, W: white, R: red, Y: yellow, B: blue, C: cyan, M: magenta)

- Eink Spectra 3000: BWR or BWY 3 color screen.
- Eink Spectra 3100: BWRY 4 color screen.
- Eink Spectra 3100 Plus: BWRY 4 color screen. The orange display is now possible with driver circuit changes.
- Eink Spectra 6: RYBW 4 color screen. Can reproduce 6 primary different colors. Newer waveforms released by Eink increased this number to 10.
- Eink Spectra 6 Plus: RYBW 4 color screen. Still reproduces 6 different colors. Allows faster refresh compared to 6 with driver circuit changes.
- Eink Gallery (also known as Gallery 4000): CMYW 4 color screen (ACeP).
- Eink Gallery Plus (also known as Gallery 4000): CMYW 4 color screen (ACeP).
- Eink Gallery Palette (also known as Gallery Palette 4000)： CMYW 4 color screen (ACeP). Reproduce 7 different colors.
- Eink Gallery 3: CMYW 4 color screen (ACeP). Reproduce 8 different colors, much faster than other Gallery screens at the cost of lower saturation.

There are both integrated-controller Spectra/Gallery screens and controller-less Spectra/Gallery screens.

Additional notes regarding the multi-pigment color screens:

- ACeP, or Advanced Color ePaper refers to the CMYW 4 color screen. Is not a product line on its own
- To be honest, I don't know how many colors can be reproduced on Gallery or Gallery Plus screens based on public information. The spec sheets for [AC133UT1](https://www.beck-elektronik.de/fileadmin/user_upload/Produkte/BECK_Elektronik/Displays/Downloads/EPD/E-Ink/AC133UT1_Specs.pdf?v=1662907755) suggests it might be 8 colors. Eink claims 32000 or 60000 colors in their materials, but they also clarified these numbers refer to color gamut. In other words, they represent color saturation rather than a number of different colors that can be displayed on screen. Dithering is heavily used to display color images on Gallery screens.
- It's possible to achieve more colors on Gallery Palette screens. 7 is not a physical limit.
- The Gallery 4000 rebranding happened in [2020](https://www.linkedin.com/pulse/e-ink-gallery-4000-anna-rybalko/) however Eink never seems to use that name on their website.

## Design of Caster and Glider

This section describes the design specific to the Caster and Glider. The following is an overall block diagram showing both hardware and gateware components in the signal chain:

### Gateware Architecture

The FPGA gateware is divided into multiple modules. The caster.v is the top-level of the EPDC core design, but several additional components are connected under top.v to form a complete image processing system. Different components are generally inter-connected with synchronous or asynchronous (in case of clock domain crossing) FIFOs.

The top-level design has 3 major clock domains: clk_vi: Input video clock domain, running at ½ pixel rate. clk_epdc: EPDC clock domain, running at ¼ pixel rate. clk_mem: Memory clock domain, running at ¼ memory transfer rate.

To understand how it works, the following is a guided tour around the life cycle of a pixel.

Before an incoming pixel can be processed by the controller, the memif module needs to retrieve the local pixel state from the DDR SDRAM. Once the value is retrieved, it’s pushed into the state readout/ input FIFO (bi_fifo). At/ around the same time, the input video stream is pushed into the video input FIFO (vi_fifo).

The EPDC runs a local Eink timing generator for counting pixels and blankings. This timing should be a slightly delayed version of the incoming video timing. Once the local timing generator determines that it needs to output the pixel soon, the EPDC logic pops out one pair of the video input and state readout and starts processing.
Two values go through the video processing pipeline:

- Stage 1: This pipeline stage waits for the FIFO to output the data.
- Stage 2: The 8-bit input image is dithered down to 1-bit and 4-bit at this stage for later use.
- Stage 3: The waveform lookup is done at this stage for 16-level grayscale modes
- Stage 4: Based on the pixel state, the new state and voltage selection value are determined at this stage.
- Stage 5: The new state is pushed into the state writeback/ out FIFO (bo_fifo) and the voltage selection is sent to the screen.

The memif module later pops out the writeback value from the bo_fifo and writes it back to the DDR SDRAM.

The EPDC always processes 4 pixels per clock. For screens with different interface widths, a rate adapter is added after the EPDC output. Some logic is duplicated 2 or 4 times (such as the waveform RAM or the pixel decision logic), while some are extended and daisy-chained (such as the error diffusion dithering unit) to achieve the 4 pixels per clock throughput.

### Firmware Functions

The MCU manages housekeeping items as described below. It uses FreeRTOS as the operating system.

- EPD power supply: The power supply provides a common, source, and gate supply to the EPD panel. In addition to a basic on/off switch, the MCU can also adjust the VCOM voltage, and measure the optimal VCOM voltage of the panel installed. The VCOM measurement is done by isolating the VCOM supply from the screen while keeping the gate supply, scanning the screen with source = VCOM, and measuring the kick-back voltage on the VCOM.
- Power supply monitoring: The microcontroller monitors voltage and current of different rails, and ensure they are in the expected range.
- FPGA bitstream loading: The FPGA doesn’t have its own flash memory, the bitstream is pushed over SPI from the MCU to the FPGA upon powering up. In this way, the FPGA bitstream can be easily bundled together with the MCU’s firmware and updated together.
- Type-C negotiation: The onboard USB Type-C port can support video input in addition to powering the board using the USB-C DisplayPort Alt Mode. The MCU runs a USB-C PD stack to communicate this capability to the video source device over standard USB PD protocol. The MCU also controls the Type-C signal mux to remap the lanes to the correct place depending on the cable orientation.
- Video decoder initialization: The FPGA used on the board doesn’t have high-speed deserializers to interface with common high-speed video interfaces such as DisplayPort or DVI directly. Instead, dedicated video decoder chips are used on the board. They typically need initialization before use, and the MCU takes care of this. In this specific design, the DP decoder chip also handles AUX P/N line flipping based on the Type-C cable orientation.
- PC communication: One advantage of the Caster is that update modes and forced update/ clearing can be applied on a per-pixel basis. Software may utilize this to assign different modes to different windows or change update modes depending on the content on the fly. This is done by sending requests to the MCU over a USB connection. The MCU runs TinyUSB and presents itself as an HID device so it can forward messages between the host PC and the FPGA.

### Low Latency Drive

The Caster implements several techniques for reducing the latency, which will be explained here.

As described before, the existing basic driving method employs a global counter for looking up the waveform table. This imposes a limit on the global image update rate: the controller only accepts a new incoming image after the previous update is finished. The update usually takes about 100ms, translating to an image rate of 10Hz. Or, in other words, the user needs to potentially wait up to 100ms before the new image is even processed by the controller.

One way to mitigate this issue is by having multiple update regions. For example, imagine the user is typing a and b. In a single region controller design, a is drawn to the screen immediately, while the b needs to wait 100ms before it gets drawn. If the controller supports multiple regions, it could start drawing the letter b as soon as it’s typed, reducing the latency. This however requires the software to program the controller to correctly set the region to the letter boundary, and re-allocating regions on the fly as the number of regions is generally quite limited (like 4-16).

The Caster simply treats every pixel as an individual update region, for maximum flexibility and is transparent to the software.

Another latency optimization technique the Caster implemented is on the pixel that’s already being updated. For example, if the user types the letter a and deletes it right after. With the basic driving method, the controller needs to wait till the letter a is fully displayed before it can erase it. The previously proposed/ implemented regional update doesn’t help here because in this situation it’s about the same pixel so it has to be in the same region. The second technique is early cancellation. If a pixel changes before it’s fully driven, instead of waiting for it to be fully driven, it’s driven toward the requested input state, and the frame counter is updated depending on the newly calculated driving time.

By combining both, it’s then possible to implement low-latency binary and 4-level grayscale modes. The tradeoff between framerate and contrast ratio is also no longer relevant. Both a high frame rate and high contrast ratio are achieved automatically.

### Hybrid Greyscale Mode

As discussed previously, getting [greyscale](#greyscale-display) image on Eink is a sophisticated process, much slower than binary, and shows flashing images during the process. This poses challenges on how to make it useful for the users.

On eReaders, the software could switch between fast and slow modes based on the action. The eReader software may also simply not support things that don’t work well on the screen. For example, there might be no scrolling but only whole page flipping. What’s being done on existing eink monitors is throwing the problem back to the user. The user simply needs to accept that the update is slow, the latency is long, and the process is flashing.

What Caster implemented is allowing it to switch between the fast binary mode and slow greyscale mode automatically on a per-pixel basis. When the input image is changed, it switches to binary mode and does the update. When the image hasn’t changed for a while, it re-renders the image in greyscale.

### Limitations

The method does come with downsides: it requires much more memory bandwidth to implement. Taking a 1080P panel as an example (roughly 120 Mp/s (million pixels per second) with reduced blanking). With the traditional method, the controller only needs the old pixel state and the new pixel state (4bpp each) to determine the voltage needed or 8-bit/ 1-byte memory read per pixel. The bandwidth requirement is then 120Mp/s x 1B/pixel = 120MB/s. One single 16-bit SDR-133 SDRAM is more than enough to handle this. The Caster currently stores a 16-bit state per pixel (for 2 sets of old pixel values and pixel-specific timer counters), and the pixel state needs to be updated per frame, so the pixel state buffer alone requires 2-byte read and 2-byte write per pixel. It then takes another 0.5-byte per pixel to read the new image value from memory. 120Mp/s x 4.5B/pixel = 540MB/s. A 16-bit DDR-333 memory is then needed to implement this. The Glider hardware uses a DDR3-800 memory to allow even higher resolution. If the controller is not integrated inside an SoC (like our case, the controller is sitting inside the monitor, not part of your PC’s CPU/GPU), it also needs to use actual low latency video interfaces like DVI or DP, instead of simpler but slower interfaces like USB or I80/SPI. This could drive up costs as well. These techniques also don't help with use cases like reading books, so commercial e-reader solutions have little reason to spend the extra trouble to implement these.

### Hardware Design Decisions

To be written (TODO)

### Resources Utilization

The following numbers are for reference only and would vary depending on RTL options and specific targets.

- 1704 FF
- 2531 LUT6
- 60 KB BRAM

## Building

### PCB

The PCB is designed with KiCAD 8.0. To get optimal results, use a 4-layer stack up with 1080 PP layers, but 2313 or 3313 are also acceptable.

### FPGA Bitstream

To build the FPGA bitstream:

#### Install Xilinx ISE 14.7

Xilinx ISE 14.7 is required for building bitstream of the FPGA. It no longer supports latest operating systems (officially only up to Windows 7), so there are 3 ways:

- Use the official RHEL virtual machine provided by Xilinx: the recommended way, should work on any modern OSes
- Use old operating system (such as Windows 7): Obvious way, but using deprecated OSes has its own implications
- Install the software anyways and find hacks to make it work: I have had luck get it running on Ubuntu 20.04, Windows 10, and Windows 11. Your mileage might vary.

The software is available for download at [https://www.xilinx.com/downloadNav/vivado-design-tools/archive-ise.html](https://www.xilinx.com/downloadNav/vivado-design-tools/archive-ise.html). The "ISE Design Suite for Windows 10 and Windows 11" is the official virtual machine. To use the virtual machine method, download this even if you are not on Windows 10/11. Otherwise, download the normal 14.7 version.

If you are using the virtual machine on platforms other than Windows 10/11, you can extract only the ova file from the zip file. The ova file can then be imported into software like VirtualBox. Note that the ISE inside the virtual machine uses the MAC address for verifying the license. Please make sure you don't change the MAC address for the NIC inside the virtual machine. (When importing, include all network adapter MAC addresses just to be sure.)

#### Clone Caster Repository

The FPGA gateware source code is hosted in a separate repository, and can be cloned by running:

```
git clone --recursive https://gitlab.com/zephray/Caster.git
```

Make sure to use the recursive flag to clone submodules as well.

#### Configuring Parameters

Most of the parameters are configured over the SPI bus from the MCU. However there are still some compile time parameters to be set before building the FPGA bitstream.

- In `rtl/spartan6/top.v`, there is a parameter called `COLORMODE`. It can be set to `MONO`, `RGBW`, or `DES`. `RGBW` should be used on OED panels, and `DES` should be used on Kaleido 3 and DES screens.
- In `rtl/defines.vh`, there is a define called `OUTPUT_16B`. Define this flag when using 16-bit panels.

Note that for both Modos kits (6" and 13"), default setting (MONO, 8-bit) is the correct setting.

#### Build FPGA Gateware using GUI

There are 2 ways to build the gateware. One is using Xilinx's ISE GUI, another is using build script. Note that on a freshly cloned repo, you will need to build with GUI at least once to re-generate all necessary IPs.

1. Open ISE Project Navigator
2. Click `Open Project...`, open `Caster/rtl/spartan6/caster.xise`
3. In the left processes pane, double click `Generate Programming File`
4. It would prompt about IP regeneration multiple times, click `Yes` every time
5. It should then build the bitstream. The output file is `rtl/spartan6/top.bit`

#### Build FPGA Gateware using script

1. Open a terminal
2. Change directory to `Caster/rtl/spartan6/par`
3. Run `build.sh` or `build.bat` depending on the OS to build the bitstream. The output file is `fpga.bit`

### MCU Firmware

To build the MCU firmware:

#### Install STM32CubeIDE

The software is freely available on ST's website: [https://www.st.com/en/development-tools/stm32cubeide.html](https://www.st.com/en/development-tools/stm32cubeide.html). It supports all 3 major operating systems.

#### Clone Glider Repository

The repository can be cloned by doing:

```
git clone --recursive https://gitlab.com/zephray/Glider.git
```

Make sure to use the recursive flag to clone submodules as well.

#### Build MCU firmware

1. Open STM32CubeIDE, launch with any workspace path (default is fine)
2. In the menu, click `File` -> `Open projects from file systems`
3. Click `Directory...` button and select `Glider/fw`, click `Open`
4. It should scan the folder and recognize it as a project, click `Finish`
5. In the `Project Explorer` pane on the left, click the `glider_ec_rtos` project to highlight it
6. Click the build icon in the toolbar (or in the menu, `Project` -> `Build Project`)
7. It should build correctly. If it complaines about missing tusb.h, it means the submodule wasn't cloned (probably because the `--recursive` flag was missing or it was downloaded from the webpage). The output is `Glider/fw/Debug/glider_ec_rtos.bin`

### Flashing Board

To flash the firmware:

- Install dfu-util (for example, `apt install dfu-util`, or `brew install dfu-util`)
- Holding the button closer to the USB port and plug in the USB cable
- Use one of the 2 methods to complete the flashing process

#### Method 1: Use the provided flashing tool

- Make sure you have a Python 3 environment and you can install packages to it
- Install `hidapi` Python package by running `pip3 install hidapi`
- Change directory into `utils/flash_tool` and copy over compiled bitstream `fpga.bit` and firmware `glider_ec_rtos.bin`
- Run the tool `python3 flash.py`

#### Method 2: Manual flashing

- Run `sudo dfu-util -l`, it should detect 2 DFU devices
- Run `sudo dfu-util -a 0 -i 0 -s 0x08000000:leave -D glider_ec_rtos.bin`
- It should show `File downloaded successfully`
- Unplug and plug in the USB cable again to reboot to the new firmware
- The board should be detected as an USB serial device (check /dev/tty*, on macOS it's something like /dev/tty.usbmodem310038002, on Linux probably /dev/ttyACM0)
- Use a serial terminal to connect to the board (I recommend use minicom for Linux, coolterm for macOS, and Tera Term for Windows)
-  Now you should be in Glider's shell. Pressing enter should show a "#" prompt. Run the `ver` command, it should report the new build date time.- Now use the shell to update the bitstream for fpga. Enter command  `recv fpga.bit` in the shell (recv is the command for receiving file over XMODEM protocol, 'fpga.bit' is the filename to save as. It would be saved to the on-board flash)
- After that, the board would start waiting for file transmission. In minicom, Press Meta-S (Ctrl-A then S on Linux) to open the upload menu. Select xmodem then select the top.bit file to transmit it. It might take up to 2 seconds to establish the transfer. There is a 10s timeout after which the board stops trying to receive the file. Just run the recv command again to retry if that happens. In other software, similarly use Xmodem transfer feature to send the file
- After the bitstream is transferred, firmware upgrade is finished
- If this is a fresh install, transfer over the font file (font_24x40.bin) using the same method as the bitstream

### Compatible Screens

The Modos Dev Kit offers two screen options: 13.3" 1600x1200 and 6" 1404x1072. However the board is capable of driving other panels as well. See [Screen Panels](#screen-panels) for differences between different types of screen panels available.

#### Screen Adapters

Different screen panels have different connectors. It would take a huge amount of space to have every possible screen connector on the motherboard. Instead, a series of different screen adapters are provided to adapt to the screen with different pinouts.

The motherboard uses a 50pin + 16pin connector. A single 50pin connector is enough for 8/16-bit screens, the 16 pin connector additionally adds support for LVDS screens and 32-bit/ 64-bit screens.

Mega adapter 1: Most common screens

- 33P-A: ED097OC1-4/TC1
- 34P-A: ED060XC3/XD4/XG1 etc.
- 39P-A: ED133UT1-3 ED050SU3 etc.
- 40P-A/B: ED078KC1 ED103TC2 etc. (A inserts with contact facing down, B inserts with contact facing up)
- 50P-A: ED113TC1

To see which adapter might work for your screen, check out the [Appendix 1 - Screen List](#screen-list)

#### Pixel Rate Considerations

The input protocol and processing rate limit the screen model supported.

Limit from processing rate (logic and routing delay):

* Processing rate when dithering enabled: 133 MP/s
* Processing rate when dithering disabled: 280 MP/s
* Estimated processing rate with 8-wide design: 500 MP/s

Limit from video interface:

* Maximum pixel rate using DVI (with ADV7611): 165 MP/s
* Maximum pixel rate using DVI (direct deserializer): 105 MP/s
* Maximum pixel rate using DisplayPort (with PTN3460): 224 MP/s
* Maximum pixel rate using DisplayPort (with 7-series 6G SerDes): 720 MP/s
* Maximum pixel rate using MIPI (with 1.05Gbps LVDS): 230 MP/s

Limit from memory interface (assuming 90% BW utilization):

* SDR-166 x16: 60 MP/s
* SDR-166 x32: 120 MP/s
* DDR-400 x16: 180 MP/s
* DDR2/3-667 x16: 300 MP/s
* DDR2/3-800 x16: 360 MP/s
* DDR2/3-1066 x16: 480 MP/s
* DDR2/3-800 x32: 720 MP/s

Common screen resolution peak pixel rate (with CVT-RBv2):

* 1024x758 (6.0") @ 85Hz: 74 MP/s
* 1448x1072 (6.0") @ 60Hz: 101 MP/s
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
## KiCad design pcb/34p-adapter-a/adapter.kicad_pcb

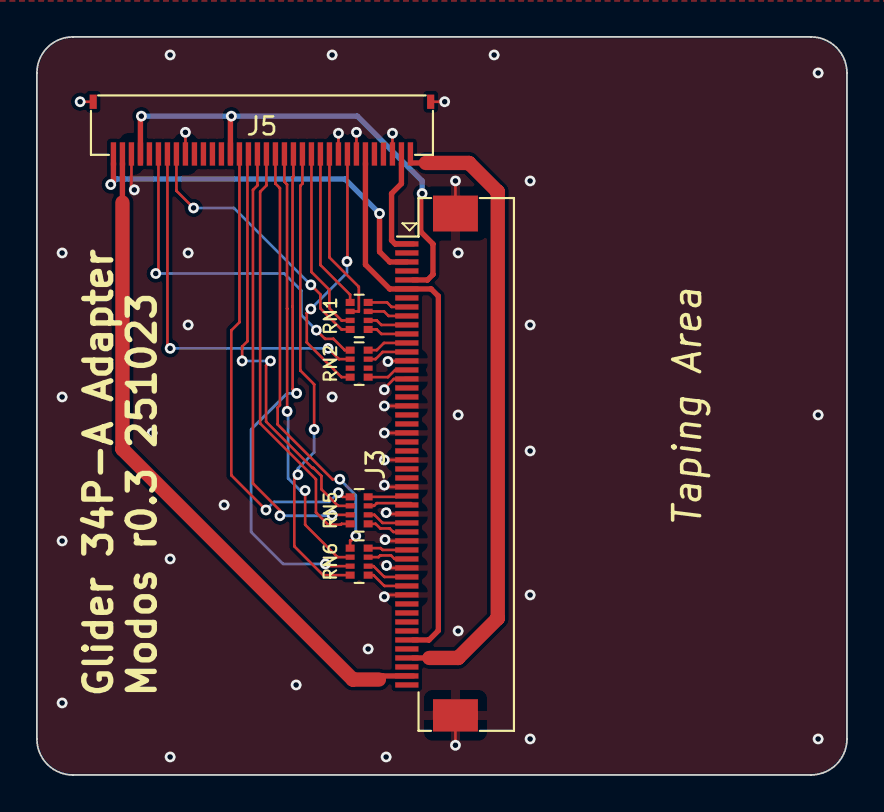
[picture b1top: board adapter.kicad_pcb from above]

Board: 2 copper layers, 45.0 x 41.0 mm, 6 parts (0 on the bottom side), 37 nets.

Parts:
J3: FPC-05F-50PH20; Xunpu_FPC-05F-50PH20_1x50-1MP_P0.50mm_Horizontal_Mirrored
J5: FH34SRJ-34S-0.5SH; Hirose_FH34SRJ-34S-0.5SH_1x34-1MP_P0.50mm_Horizontal
RN1, RN2, RN5, RN6: 33; R_Array_Convex_4x0402

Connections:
+3V3: J3.6, J3.45, J5.6
+VGH: J3.3, J5.34
+VP: J3.49, J5.33
-VCOM: J3.5, J5.21, J5.31
-VGL: J3.1, J5.2
-VN: J3.47, J5.1
/ED0: J5.13, RN6.8 (R1.2)
/ED1: J5.14, RN6.7 (R2.2)
/ED2: J5.15, RN6.6 (R3.2)
/ED3: J5.16, RN6.5 (R4.2)
/ED4: J5.17, RN5.8 (R1.2)
/ED5: J5.18, RN5.7 (R2.2)
/ED6: J5.19, RN5.6 (R3.2)
/ED7: J5.20, RN5.5 (R4.2)
/ESDCLK: J5.8, RN2.8 (R1.2)
/ESDLE: J5.10, RN1.6 (R3.2)
/ESDOE: J5.11, RN1.5 (R4.2)
/GDCLK: J5.28, RN2.6 (R3.2)
/GDOE: J5.27, RN1.8 (R1.2)
/GDSP: J5.29, RN2.5 (R4.2)
/PD0: J3.39, RN6.1 (R1.1)
/PD1: J3.38, RN6.2 (R2.1)
/PD2: J3.36, RN6.3 (R3.1)
/PD3: J3.35, RN6.4 (R4.1)
/PD4: J3.33, RN5.1 (R1.1)
/PD5: J3.32, RN5.2 (R2.1)
/PD6: J3.30, RN5.3 (R3.1)
/PD7: J3.29, RN5.4 (R4.1)
/PGDCLK: J3.13, RN2.3 (R3.1)
/PGDOE: J3.11, RN1.1 (R1.1)
/PGDSP: J3.12, RN2.4 (R4.1)
/PSDCE0: J3.10, RN1.2 (R2.1)
/PSDCLK: J3.15, RN2.1 (R1.1)
/PSDLE: J3.9, RN1.3 (R3.1)
/PSDOE: J3.8, RN1.4 (R4.1)
/SDCE0: J5.12, RN1.7 (R2.2)
GND: J3.14, J3.16, J3.19, J3.22, J3.25, J3.28, J3.31, J3.34, J3.37, J3.40, J3.MP (MountPin), J5.3, J5.7, J5.9, J5.26, J5.32

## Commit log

2025-09-10 Example printable cases for Glider kits
2025-09-10 PCB r1p3
2025-11-23 Optimize flash format speed
2025-12-22 Update README about building process
2025-12-27 Improve PD reliability; Fix USB descriptors
2025-12-27 Sync local PCB changes
2026-01-26 Use SDR mode for ADV7611
2026-03-03 Upload updated case designs
2026-03-20 Update case design
2026-06-28 Fix compilation warnings and errors under GCC 15
2026-06-28 fw: restore global dither mode on standby wake

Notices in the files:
README.md:
License:
This document, other than references explicitly given with their corresponding license, is released into the public domain.
The hardware design is released under the CERN Open Source Hardware License strongly-reciprocal variant, CERN-OHL-S. A copy of the license is provided in the source repository. Additionally, a user guide of the license is provided on ohwr.org.
The firmware code is licensed under the MIT license with the following exceptions: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
